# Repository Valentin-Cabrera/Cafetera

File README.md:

# Cafetera
## Diseño del control de cafetera comercial.

La cafetera cuenta con una serie de sensores que monitorean la presión y temperatura del boiler en todo momento. A su vez, la presión necesaria para extraer el café es generada por una bomba rotatoria conectada a un motor de inducción monofásico.

Como objetivo, me planteo el diseño de un variador de frecuencia que permita regular la presión de extracción del café, variando las RPM del motor. Además de esto, el controlador también deberá monitorear los distintos sensores de presión y temperatura en el boiler.

El paso de agua está controlado por una serie de válvulas solenoides que funcionan directamente a 220 V 50 Hz, por lo que será necesario utilizar relés para su control.

## Módulos del diseño

Dadas las características deseadas, voy a dividir el diseño del controlador en dos partes:

- Potencia
- Lógica

Para la parte de potencia, implementaré un variador de frecuencia con MOSFETs en un puente H. En particular, se utilizarán 2 NMOS y 2 PMOS junto con dos optoacopladores que garanticen aislamiento galvánico entre ambos módulos.

Para la parte lógica, utilizaré un Arduino Nano, 4 relés (3 para válvulas y 1 para la resistencia del boiler), un sensor de presión para monitorear la salida de la bomba, un termistor y un ADS1115 para realizar las mediciones de los sensores. 
## Esquemático del variador de frecuencia (circuito de potencia)

### Lista de componentes:
- IRFP460PBF
- IXTH10P50P
- 4N35
- GBJ2510-BP
  
Falta dimensionar los valores de las resistencias para la correcta carga y descarga de los gates de los MOSFETs, además del cálculo de la capacidad para mantener un ripple pequeño.
## Simulación con componentes similares.

## Esquematico de PCB encargada de la logica (Pendiente)

## Siguiente paso 
Para continuar con el desarrollo hace falta el ensamblado y testeo de la parte de potencia, ensayo de arranque del motor (para chequear que las pistas de la pcb y componentes puedan soportar el transistorio). Posteriormete la calibración de los sensores para comporbar el correcto funcionamiento de la cafetera con el controlador diseñado.

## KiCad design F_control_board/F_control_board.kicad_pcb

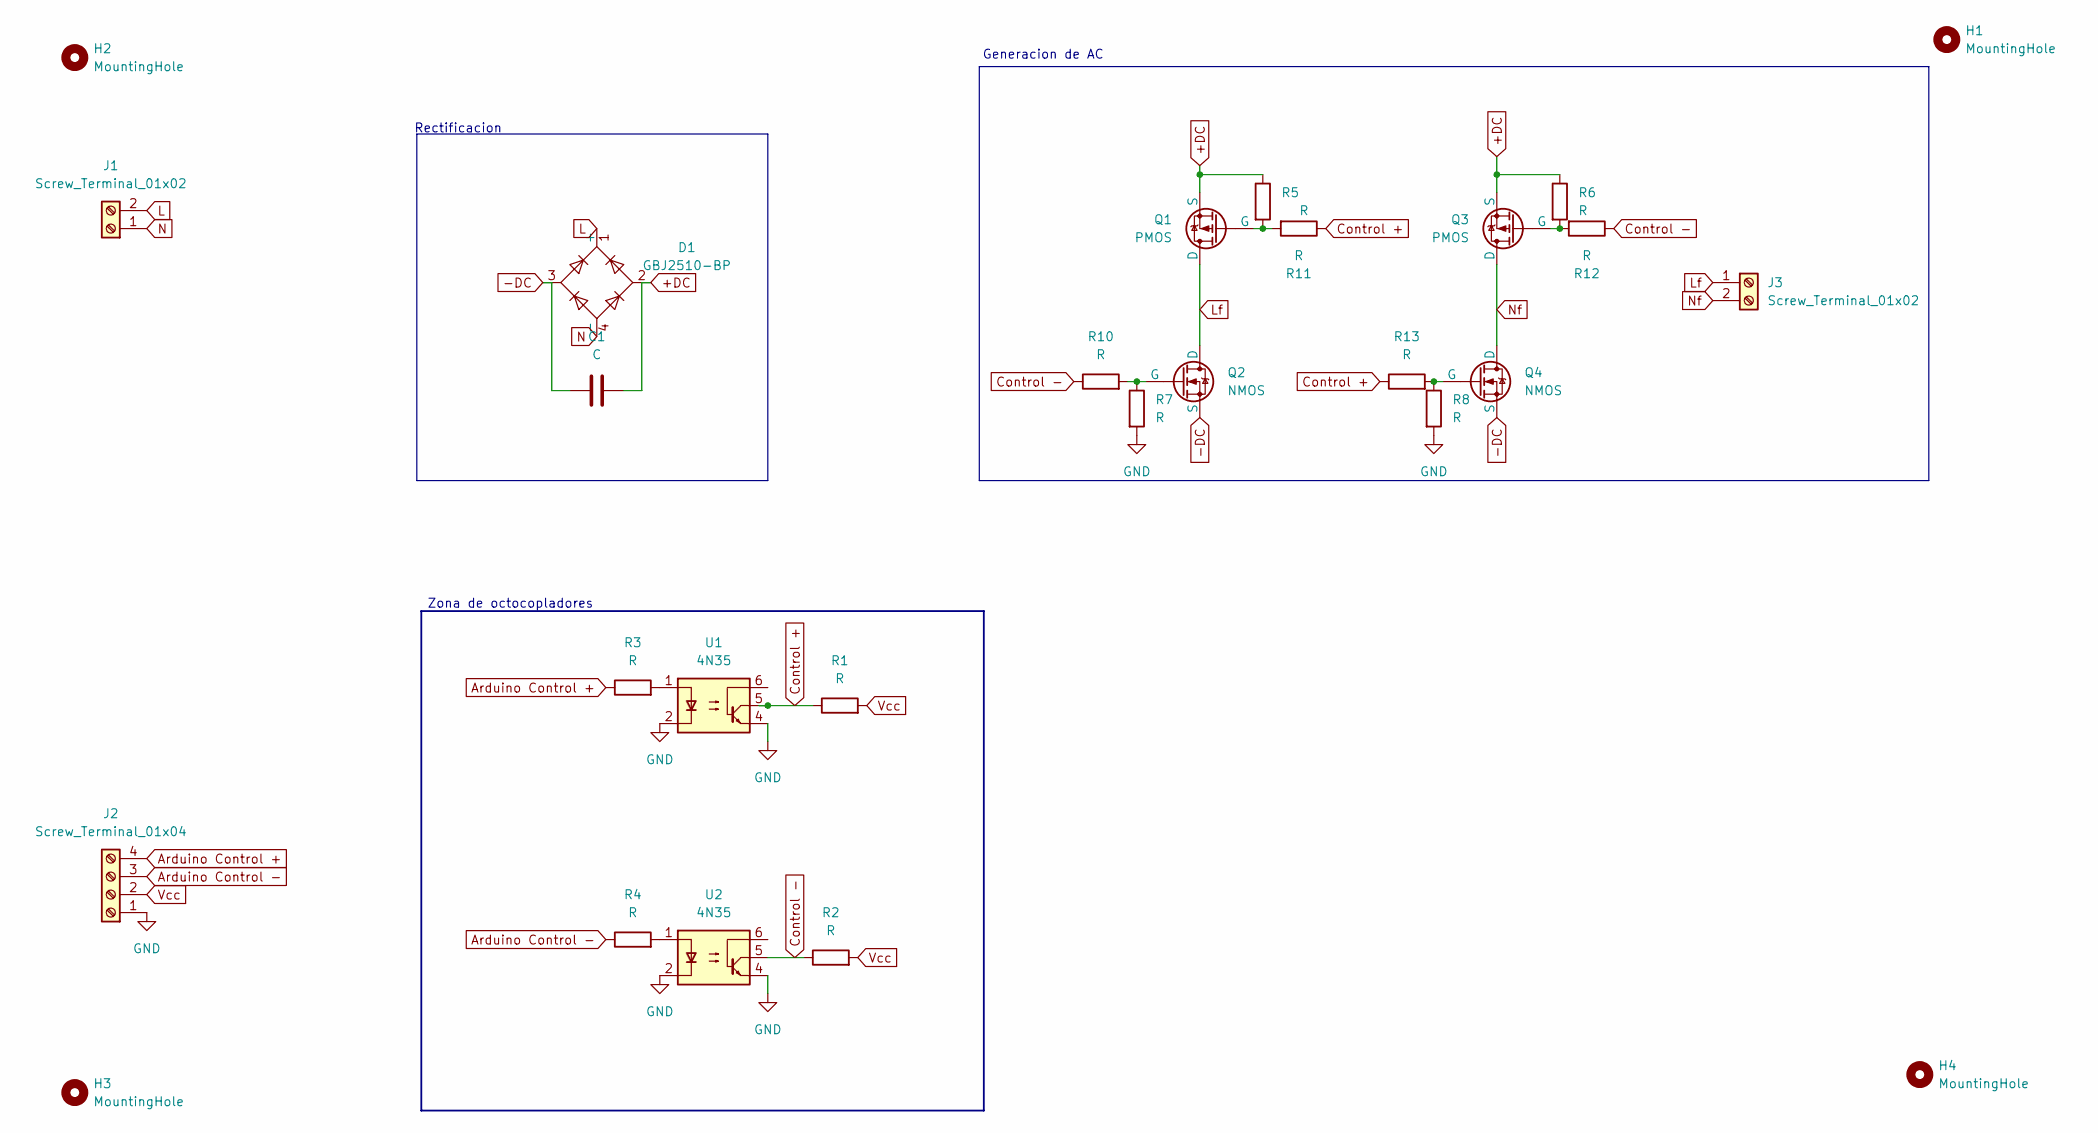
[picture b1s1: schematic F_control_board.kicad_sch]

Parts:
C1: C; CP_Radial_D10.0mm_P2.50mm
D1: GBJ2510-BP; Diode_Bridge_Vishay_GBU
H1, H2, H3, H4: MountingHole; MountingHole_2.2mm_M2_DIN965_Pad
J1, J3: Screw_Terminal_01x02; TerminalBlock_RND_205-00241_1x02_P10.16mm_Horizontal
J2: Screw_Terminal_01x04; TerminalBlock_MaiXu_MX126-5.0-04P_1x04_P5.00mm
Q1, Q3: PMOS; TO-247-3_Vertical
Q2, Q4: NMOS; TO-247-3_Vertical
R1, R2, R3, R4, R5, R6, R7, R8, R10, R11, R12, R13: R; R_Axial_DIN0204_L3.6mm_D1.6mm_P7.62mm_Horizontal
U1, U2: 4N35; DIP-6_W7.62mm

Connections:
+DC: C1.2, D1.2, Q1.3 (S), Q3.3 (S), R5.1, R6.1
-DC: C1.1, D1.3, Q2.3 (S), Q4.3 (S)
Arduino Control +: J2.4, R3.1
Arduino Control -: J2.3, R4.1
Control +: R1.1, R11.1, R13.1, U1.5
Control -: R2.1, R10.1, R12.1, U2.5
GND: J2.1, R7.2, R8.2, U1.2, U1.4, U2.2, U2.4
L: D1.1 (+), J1.2
Lf: J3.1, Q1.1 (D), Q2.1 (D)
N: D1.4 (-), J1.1
unnamed: Q1.2 (G), R5.2, R11.2
unnamed: Q2.2 (G), R7.1, R10.2
unnamed: Q3.2 (G), R6.2, R12.2
unnamed: Q4.2 (G), R8.1, R13.2
unnamed: R3.2, U1.1
unnamed: R4.2, U2.1
Nf: J3.2, Q3.1 (D), Q4.1 (D)
Vcc: J2.2, R1.2, R2.2

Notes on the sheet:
Generacion de AC
Rectificacion
Zona de octocopladores

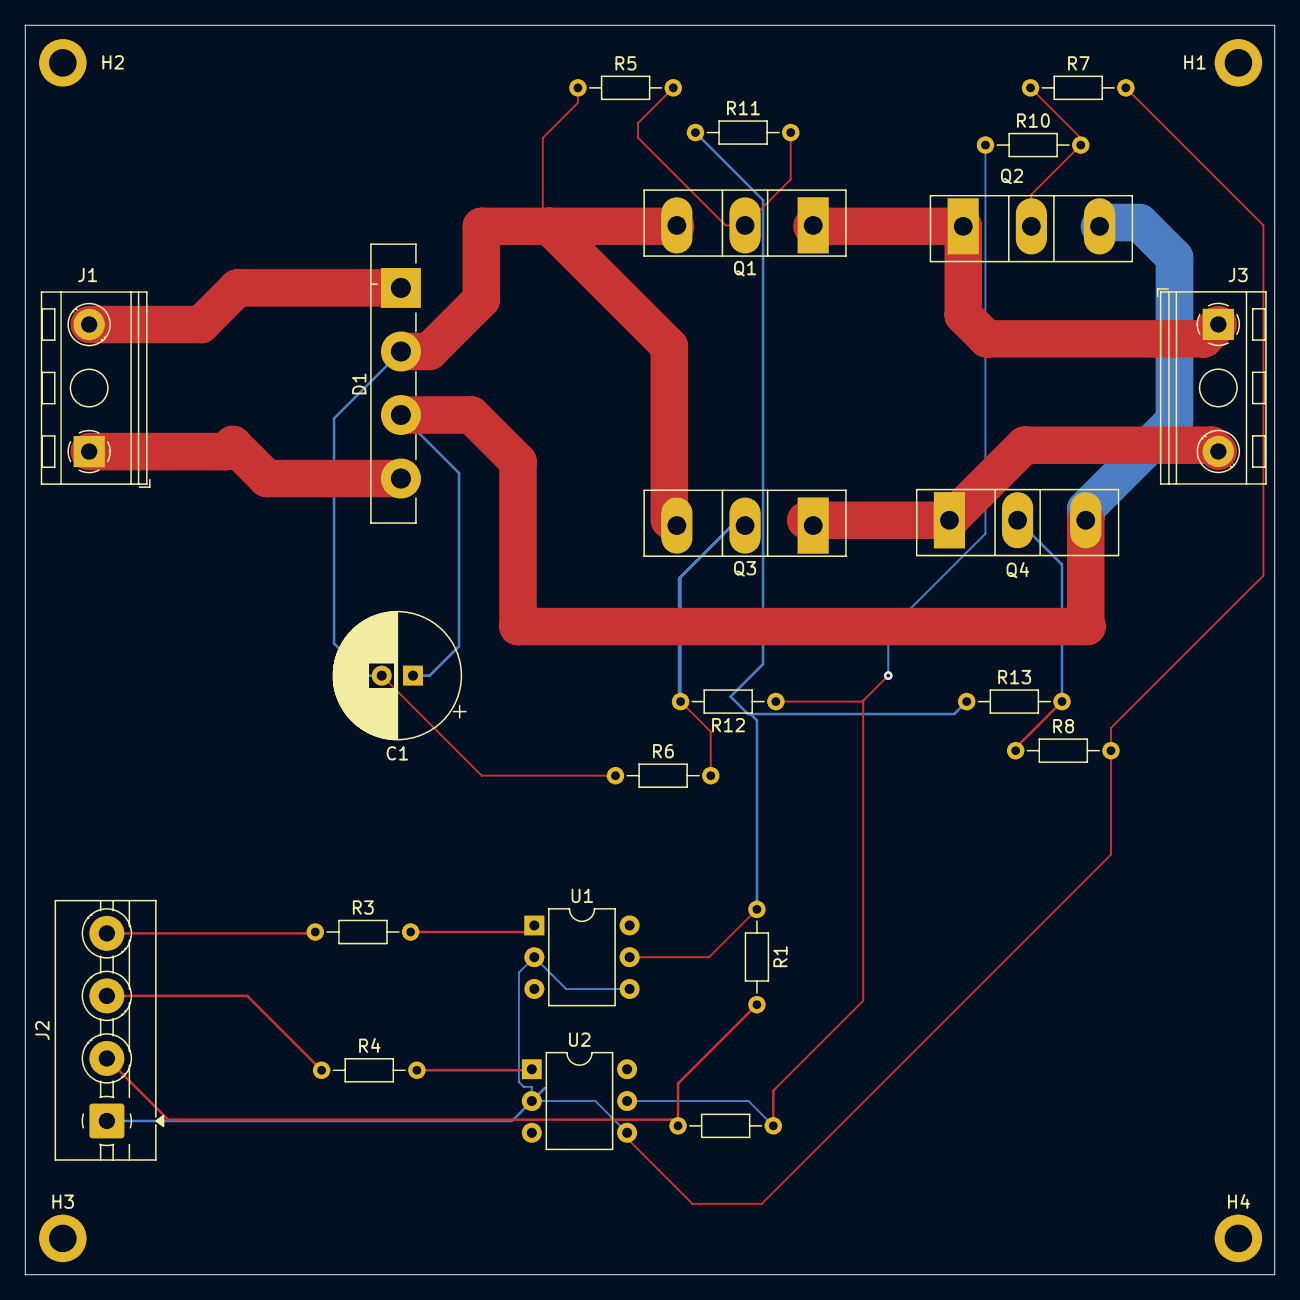
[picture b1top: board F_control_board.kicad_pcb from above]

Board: 2 copper layers, 99.9 x 99.9 mm, 27 parts (0 on the bottom side), 18 nets.
